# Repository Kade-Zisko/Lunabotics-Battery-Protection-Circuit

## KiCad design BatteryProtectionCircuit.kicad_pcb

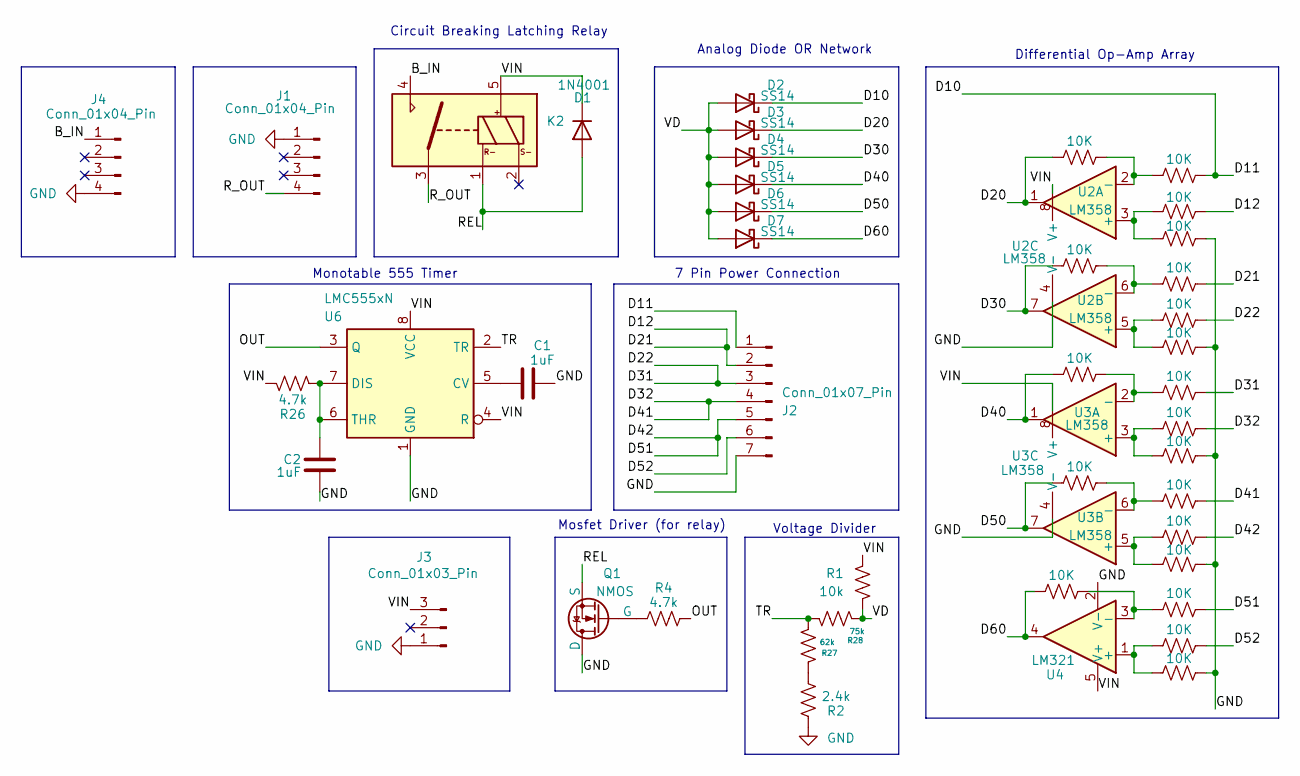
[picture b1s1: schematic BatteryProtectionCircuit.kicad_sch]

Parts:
C1, C2: 1uF; C_0805_2012Metric
D1: 1N4001; D_DO-41_SOD81_P10.16mm_Horizontal
D2, D3, D4, D5, D6, D7: SS14; D_SMA
J1, J4: Conn_01x04_Pin; CONN2_2606-1102_WAG
J2: Conn_01x07_Pin; JST_XH_B7B-XH-AM_1x07_P2.50mm_Vertical
J3: Conn_01x03_Pin; JST_XH_B3B-XH-AM_1x03_P2.50mm_Vertical
K2: CONN5_21105_PAN
Q1: NMOS; SOT-23
R1: 10k; R_0805_2012Metric
R2: 2.4k; R_0805_2012Metric
R4, R26: 4.7k; R_0805_2012Metric
R5, R6, R7, R8, R9, R10, R11, R12, R13, R14, R16, R17, R18, R19, R20, R21, R22, R23, R24, R25: 10K; R_0805_2012Metric
R27: 62k; R_0805_2012Metric
R28: 75k; R_0805_2012Metric
U2, U3: LM358; DIP-8_W7.62mm
U4: LM321; SOT-23-5
U6: LMC555xN; DIP-8_W7.62mm

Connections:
/B_IN: J4.1, K2.4
/D10: D2.1 (K), J2.1, R5.2
/D12: J2.2, R7.2, R9.2
/D20: D3.1 (K), R6.1, U2.1
/D22: J2.3, R11.2, R13.2
/D30: D4.1 (K), R10.1, U2.7
/D32: J2.4, R14.2, R17.2
/D40: D5.1 (K), R23.1, U3.1
/D42: J2.5, R18.2, R20.2
/D50: D6.1 (K), R24.1, U3.7
/D52: J2.6, R21.2
/D60: D7.1 (K), R25.1, U4.4
/OUT: R4.1, U6.3 (Q)
/REL: D1.2 (A), K2.1, Q1.3 (S)
/R_OUT: J1.4, K2.3
/TR: R27.2, R28.1, U6.2 (TR)
/VD: D2.2 (A), D3.2 (A), D4.2 (A), D5.2 (A), D6.2 (A), D7.2 (A), R1.2, R28.2
/VIN: D1.1 (K), J3.3, K2.5, R1.1, R26.1, U2.8 (V+), U3.8 (V+), U4.5 (V+), U6.4 (R), U6.8 (VCC)
GND: C1.2, C2.1, J1.1, J2.7, J3.1, J4.4, Q1.1 (D), R2.2, R8.2, R12.2, R16.2, R19.2, R22.2, U2.4 (V-), U3.4 (V-), U4.2 (V-), U6.1 (GND)
unnamed: Q1.2 (G), R4.2
unnamed: R2.1, R27.1
unnamed: R7.1, R8.1, U2.3 (+)
unnamed: R5.1, R6.2, U2.2 (-)
unnamed: R11.1, R12.1, U2.5 (+)
unnamed: R9.1, R10.2, U2.6 (-)
unnamed: R14.1, R16.1, U3.3 (+)
unnamed: R13.1, R23.2, U3.2 (-)
unnamed: R18.1, R19.1, U3.5 (+)
unnamed: R17.1, R24.2, U3.6 (-)
unnamed: R21.1, R22.1, U4.1 (+)
unnamed: R20.1, R25.2, U4.3 (-)
unnamed: C1.1, U6.5 (CV)
unnamed: C2.2, R26.2, U6.6 (THR), U6.7 (DIS)

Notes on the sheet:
7 Pin Power Connection
Mosfet Driver (for relay)
Voltage Divider
Monotable 555 Timer
Analog Diode OR Network
Circuit Breaking Latching Relay
Differential Op-Amp Array

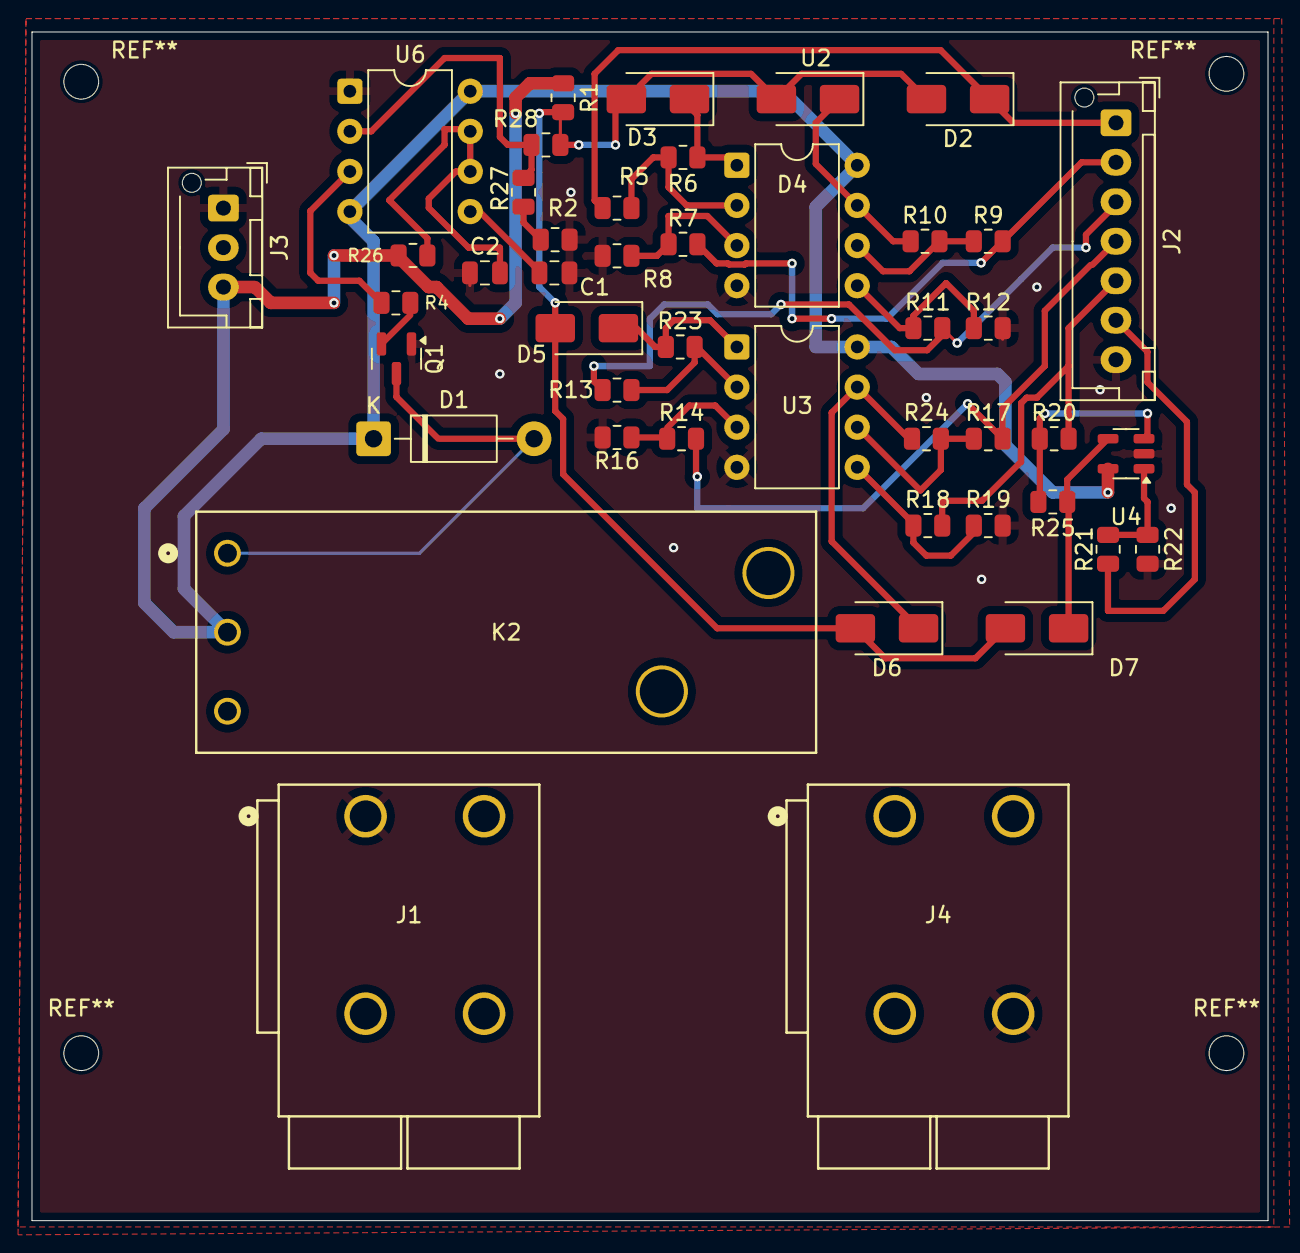
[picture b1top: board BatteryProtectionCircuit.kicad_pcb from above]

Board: 2 copper layers, 78.3 x 75.2 mm, 45 parts (0 on the bottom side), 33 nets.

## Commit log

2025-10-10 Initial Download
2025-10-18 Added requirements text file for reference
2025-10-18 Added requirements text file
2025-10-18 Added initial power supply and wiring
2025-10-18 BPC timer module complete (for 1 cell)
2025-10-21 Finished 555 based Protection Circuit for Singular Cell
2025-10-21 Added Flyback Diode to Relay to Prevent Voltage Spiking
2025-10-22 Added op-amps and diode-and network to filter out smallest voltage out of all battery cells
2025-10-22 Changed Relay to Latched Double Coil
2025-10-25 Added footprints for all components
    Besides relay
2025-10-25 Cleaned up schematic
2025-10-25 Added different relay
2025-10-25 Changed file name
2025-10-27 Fixed voltage divider values
2025-10-27 Cleaned up circuit so it doesn't explode
2025-11-08 Added New Organized Schematic with Fixed Op-Amp Array
2025-11-08 Added PDF Picture of Circuit
2025-11-08 Fixed based on Design Review Feedback
2025-12-03 Updated voltage divider values
2025-12-03 ERC check fixes
2025-12-03 Footprints + PCB
    Added footprints to schematic and started with preliminary PCB layout and routing, likely to change.
2025-12-03 Added LTSPICE simulation of circuit
2025-12-04 Switched Relay
2025-12-04 Added Op Amp
2025-12-10 Changes to routing
2025-12-10 LTSPICE simulation + Voltage Divider Fixes
2025-12-13 Added Connectors for power rail and robot input
2025-12-13 Added LTSPICE sim file
2026-01-21 Finalized(?) PCB tracing
2026-01-31 Updated Trace Widths
